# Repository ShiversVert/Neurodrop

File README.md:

# Neurodrop
## Repository for iGEM Grenoble 2019 Engineering team

### What is Neurodrop ?
Our project’s goal is to represent the universities of Grenoble at the international synthesis biologycompetition iGEM. This competition will take place at the MIT (Massachusetts Institute of Technology) between the 31st of October and the 4th of November 2019.

Our project’s aim is to create a system able to detect the presence of biomarkers in small volumes of non-complex fluids (tears, sweat, urine...). This idea comes from a conference given on June 2018by Mark Lew at the American Academy of Neurology’s 70th Annual Meeting, where he showedresults that a biomarker of Parkinson’s disease could be detected in the tears of a patient.

After a few months of researches, we realized that the idea of having a system only able to detect a biomarker for Parkinson’s disease was a reducing perspective and an idea that posed ethical problemsas there are no treatment for this pathology.That is why we enlarged our project to aim at creating a device that could be easily adapted to the detection of other biomarkers, and that could do it with as few manipulations from health technicians as possible.

Our project is then to create a system that automates the detection of all kind of biomarkers in reduced volume.In order to clarify the project, we will focus on the detection of only one biomarker that we know could be of interest for the diagnosis of Parkinson’s disease: the α−synuclein. This protein forms oligomers which concentration increases in the tears of patients with Parkinson’s.

### What's on this git ?

This repository contains the whole develeopment process for the engineering team including both hardware conception and software development.

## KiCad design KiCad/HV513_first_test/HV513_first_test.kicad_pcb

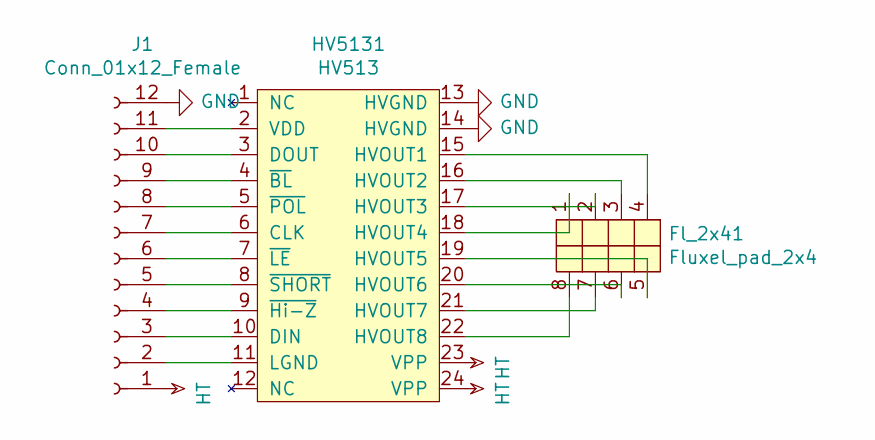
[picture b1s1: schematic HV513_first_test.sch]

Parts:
Fl_2x41: Fluxel_pad_2x4; Fluxel_matrix_2x8
HV5131: HV513; Female_Pin_Mount
J1: Conn_01x12_Female; PinHeader_1x12_P2.54mm_Vertical

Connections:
GND: HV5131.13 (HVGND), HV5131.14 (HVGND), J1.12
HT: HV5131.23 (VPP), HV5131.24 (VPP), J1.1
unnamed: Fl_2x41.1, HV5131.18 (HVOUT4)
unnamed: Fl_2x41.2, HV5131.17 (HVOUT3)
unnamed: Fl_2x41.3, HV5131.16 (HVOUT2)
unnamed: Fl_2x41.4, HV5131.15 (HVOUT1)
unnamed: Fl_2x41.5, HV5131.19 (HVOUT5)
unnamed: Fl_2x41.6, HV5131.20 (HVOUT6)
unnamed: Fl_2x41.7, HV5131.21 (HVOUT7)
unnamed: Fl_2x41.8, HV5131.22 (HVOUT8)
unnamed: HV5131.2 (VDD), J1.11
unnamed: HV5131.3 (DOUT), J1.10
unnamed: HV5131.4 (~BL), J1.9
unnamed: HV5131.5 (~POL), J1.8
unnamed: HV5131.6 (CLK), J1.7
unnamed: HV5131.7 (~LE), J1.6
unnamed: HV5131.8 (~SHORT), J1.5
unnamed: HV5131.9 (~Hi-Z), J1.4
unnamed: HV5131.10 (DIN), J1.3
unnamed: HV5131.11 (LGND), J1.2

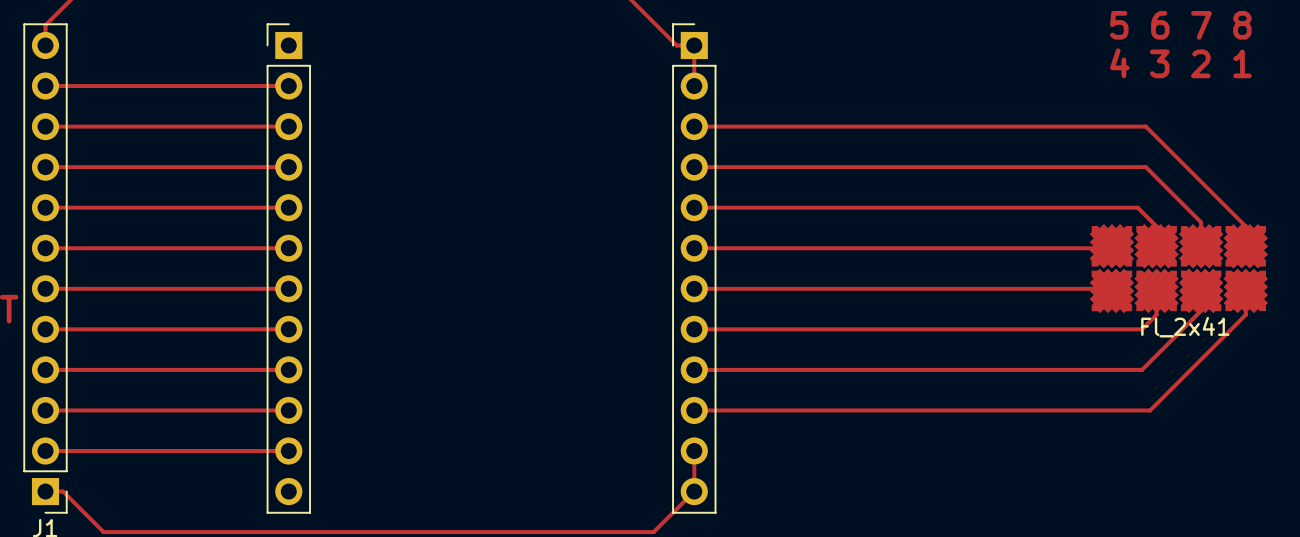
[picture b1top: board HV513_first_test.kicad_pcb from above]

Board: 2 copper layers, 3 parts (0 on the bottom side), 20 nets.

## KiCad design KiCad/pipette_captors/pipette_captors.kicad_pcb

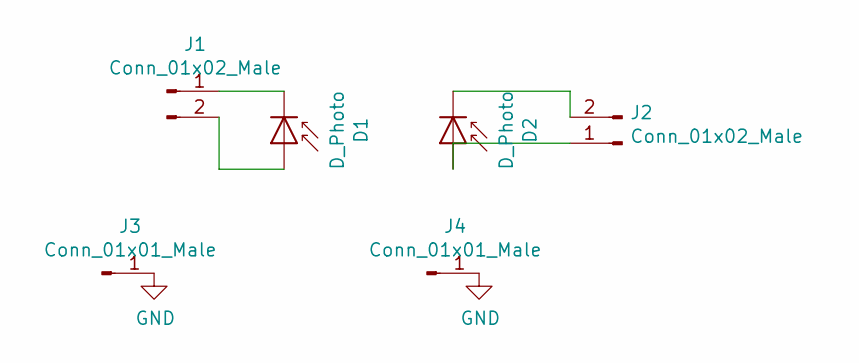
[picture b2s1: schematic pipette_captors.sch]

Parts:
D1, D2: D_Photo; R_1206_3216Metric_Pad1.42x1.75mm_HandSolder
J1, J2: Conn_01x02_Male; PinHeader_1x02_P2.54mm_Vertical
J3, J4: Conn_01x01_Male; PinSocket_1x01_P2.54mm_Vertical

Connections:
GND: J3.1, J4.1
unnamed: D1.1 (K), J1.1
unnamed: D1.2 (A), J1.2
unnamed: D2.1 (K), J2.2
unnamed: D2.2 (A), J2.1

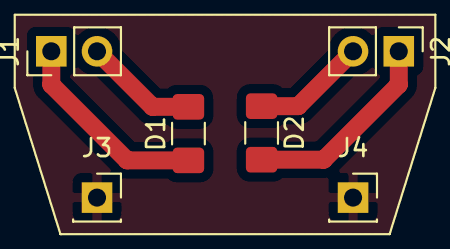
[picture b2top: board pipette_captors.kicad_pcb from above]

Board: 2 copper layers, 6 parts (0 on the bottom side), 5 nets.

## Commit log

2019-06-12 Initial commit
    Initial commit containing :
    - Some visual creations for neurodrop
    - Some Arduino code tests
    - Some Kicad files for both the pipette and the EWOD
2019-06-12 Add Arduino_files
2019-07-03 New stable version
    Last stable version
